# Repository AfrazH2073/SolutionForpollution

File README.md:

# SolutionForpollution
GitHub Repo for ECE 196 Project Managing code, PCB files, 3D design, and more.

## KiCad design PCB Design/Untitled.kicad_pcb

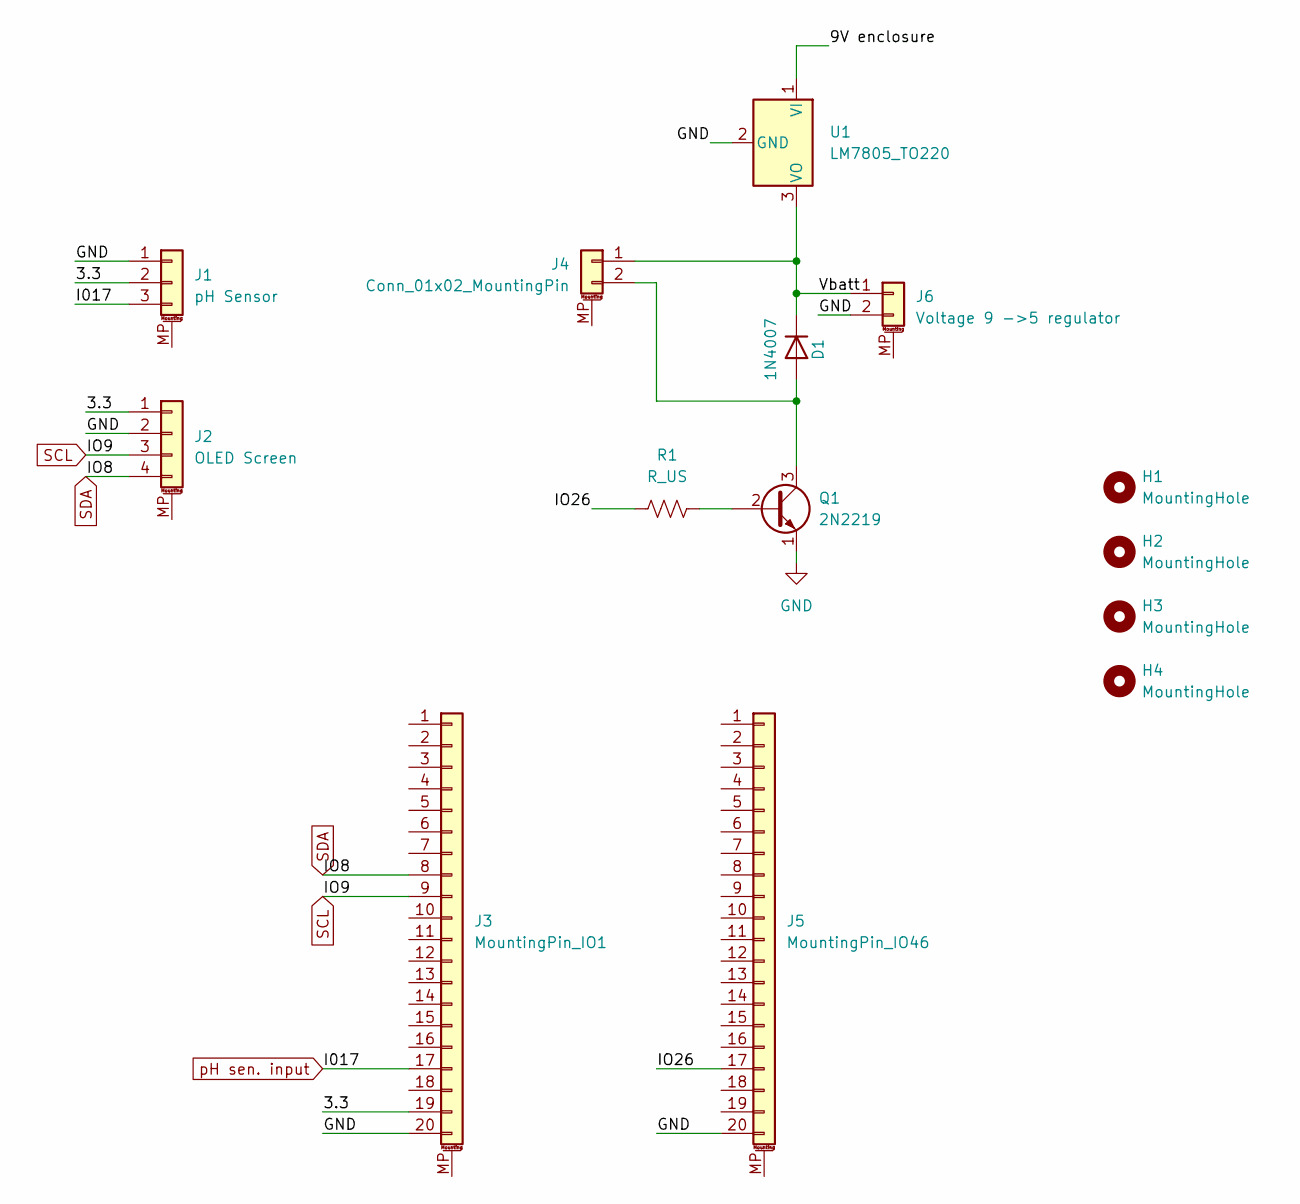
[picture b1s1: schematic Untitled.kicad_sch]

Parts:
D1: 1N4007; D_DO-41_SOD81_P10.16mm_Horizontal
H1, H2, H3, H4: MountingHole; MountingHole_3.2mm_M3_ISO7380_Pad_TopBottom
J1: pH Sensor; PinHeader_1x03_P2.54mm_Vertical
J2: OLED Screen; PinHeader_1x04_P2.54mm_Vertical
J3: MountingPin_IO1; PinHeader_1x20_P2.54mm_Vertical
J4: Conn_01x02_MountingPin; PinHeader_1x02_P2.54mm_Vertical
J5: MountingPin_IO46; PinHeader_1x20_P2.54mm_Vertical
J6: Voltage 9 ->5 regulator; PinHeader_1x02_P2.54mm_Vertical
Q1: 2N2219; TO-39-3
R1: R_US; R_2512_6332Metric
U1: LM7805_TO220; TO-220-3_Vertical

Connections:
/3.3: J1.2, J2.1, J3.19
/9V enclosure: U1.1 (VI)
/IO26: J5.17, R1.1
/Vbatt: D1.1 (K), J4.1, J6.1, U1.3 (VO)
GND: J1.1, J2.2, J3.20, J5.20, J6.2, Q1.1 (E), U1.2 (GND)
unnamed: D1.2 (A), J4.2, Q1.3 (C)
unnamed: Q1.2 (B), R1.2
SCL: J2.3, J3.9
SDA: J2.4, J3.8
pH sen. input: J1.3, J3.17

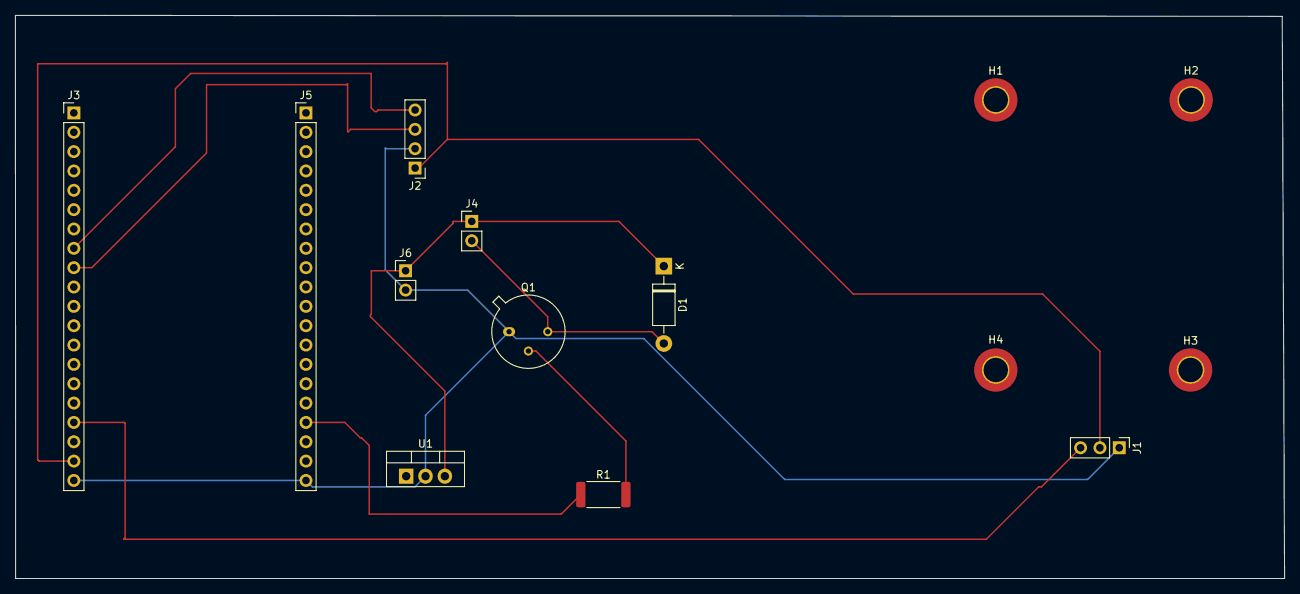
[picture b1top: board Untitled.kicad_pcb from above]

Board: 2 copper layers, 166.6 x 73.9 mm, 14 parts (0 on the bottom side), 9 nets.

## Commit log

2024-10-22 making a layout of the website
2024-10-22 fixed connections for website
2024-10-22 updated html
2024-10-22 homepage okay, starting on teammates html
2024-10-22 made layout for teammates section
2024-10-22 added pictures for everyone
2024-10-22 added milestones and timelines
2024-10-22 added favorites stuff
2024-10-22 added schematics
2024-10-22 added video layout
2024-10-22 fixed a bug
2024-10-22 added poster layout
2024-10-22 fixed title meep
2024-10-22 fixed defs on main.py
2024-10-22 added updates on main.py
2024-10-22 added structure of what files contains
2024-10-24 added pictures in team section
2024-10-24 change menu bar for each section
2024-10-24 PCB Design Initiation
    Started designs for PCB Files Kicad
2024-10-25 added theme in homepage...comp:chrome,edge,firefox,opera,safari
2024-10-28 Mini Projects
    added template mini project descriptions
2024-10-28 Commmitt
    added tempalte reosurce stuff
2024-11-04 updating
